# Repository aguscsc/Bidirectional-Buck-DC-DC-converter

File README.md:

# Bidirectional Buck DC-DC Converter

This repository documents the design and implementation of a **bidirectional DC-DC converter**.  
The system can operate in both **buck mode** (step-down) and **boost mode** (step-up), enabling power flow in both directions.  

---
## Software used
- **Simulation**
  
   Multisim, Ltspice and MATLAB/Simulink
   coil64
- **PCB**
  
   Kicad
## 📐 Specifications
- **Switching frequency**: 60 kHz  
- **Maximum power**: 5 W  

### Buck Mode
- $V_{in, min} = 23V$  
- $V_{out, max} = 14V$  

### Boost Mode
- $V_{in, min} = 12V$  
- $V_{out, max} = 27V$  

---

## 🔌 Topology
The selected topology is based on a **bidirectional synchronous buck/boost converter**.  
Diagram (preliminary):  

---

## 📊 Design Parameters
### Inductor
- To be dimensioned based on:  
 $L = \frac{V_L \cdot D}{\Delta I_L \cdot f_s}$
  where:
  - \( $V_L$ \) = inductor voltage  
  - \( $D$ \) = duty cycle  
  - \( $\Delta I_L$ \) = current ripple (≈ $30$% of \( $I_{L,max}$ \))  
  - \( $f_s$ \) = switching frequency
  
   $I_{sat} = \frac{B_{sat}\cdot l}{\mu_{0}\cdot \mu_{r}\cdot N}$
  Where:
  - \($I_{sat}$\) = Saturation current
  - \($B_{sat}$\) = saturation flux density of the core material
  - \($l$\) = effective magnetic path length of the core
  - \($\mu_{0}$\) = permeability of a vacuum
  - \($\mu_{r}$\) = relative permeability of the material
  - \($N$\) = number of turns

Recommendation: use coil64 to check your calculations, research skin effect and how different AWG interact with the frequency you're using (https://en.wikipedia.org/wiki/Skin_effect).
### Capacitor
- To be dimensioned from capacitor current balance:
- buck
  $C = \frac{\Delta I_L}{\Delta V \cdot f_s\cdot 8}$
- boost
  $C = \frac{I_{out} \cdot D}{\Delta V \cdot f_s}$
  
  where:
  - \( $\Delta V$ \) = allowed voltage ripple  

## Schematic & PCB layout

---
# Prototyping 
This section breaks down the process of prototyping and testing, the pcb in the design directory contains all the measures necessary to ensure the converter is working properly (value of components can be adjusted to your needs).
## BOM:
- 2 electrolytic capacitors $6.8\mu F$ and $2.2\mu F$ 50V each. 
- 2 ceramic capacitors (100nF).
- core T106-26 + 9m of AWG 26 wire (higher permeability would also work if the saturation stays sensible).
- 2 IFRZ44N (great for prototyping and testing)
- IR2184 driver (it can generate both MOSFET signals)
- 2 10 ohm gate resistors 1W (it limits the gate current)
- 2 10k ohm pull-down resistor 1W (drains the gate source capacitance)
 
## Measurements and tests
### switching
First, you ought to make sure the MOSFET are switching correctly. For this, turn on the pwm signal and your VCC source, then measure the gate-source pins of each MOSFET with an oscilloscope and make sure the signals are the complement of each other and respond to the change in duty. Aditionally, you should measure the gate current to ensure it is not exceeding the drivers capacity.

### Powering the circuit
Check the waveforms of the inductor current and output voltage, ideally you should be looking at two saw-like waves with minimal ripple.

Once you have ensured the inductor current and the output voltage have satisfied your needs you can proceed to measure the converters effiency for each mode.

Note: if you struggle achieving the voltage ripple required, considering soldering ceramic capacitors parallel to your current ones.
### Efficiency 
**BUCK** R = $39.8$

| Duty | $V_{in}$ | $I_{in}$ | $V_{out}$ | $P_{in}$ | $P_{out}$ | Efficiency |
|:----:|:---------:|:---------:|:----------:|:---------:|:----------:|:-----------:|
| 35%  | 23 V | 0.06 A | 7.26 V | 1.38 W | 1.32 W | 96.4 % |
| 45%  | 23 V | 0.10 A | 9.45 V | 2.30 W | 2.24 W | 97.5 % |
| 55%  | 23 V | 0.16 A | 11.6 V | 3.68 W | 3.38 W | 91.8 % |
| 65%  | 23 V | 0.22 A | 13.78 V | 5.06 W | 4.77 W | 94.3 % |

**BOOST** R = $142.2$

| Duty | $V_{in}$ | $I_{in}$ | $V_{out}$ | $P_{in}$ | $P_{out}$ | Efficiency |
|:----:|:---------:|:---------:|:----------:|:---------:|:----------:|:-----------:|
| 29.5%  | 12 V | 0.16 A | 16.34 V | 1.92 W | 1.87 W | 97.7 % |
| 39.5%  | 12 V | 0.21 A | 18.79 V | 2.52 W | 2.48 W | 98.5 % |
| 49.5%  | 12 V | 0.30 A | 22.11 V | 3.60 W | 3.43 W | 95.4 % |
| 59.5%  | 12 V | 0.46 A | 26.77 V | 5.52 W | 5.04 W | 91.3 % |

# PWM control
Previously, the pwm signal was generated with a waveform generator, for real applications this has to be implemented with a microcontroller, in this case we'll use a PIC32 to generate the pwm signal.
This section will cover the programming and testing of the control system and its integration with the power circuit.

## Prototyping

First the [Curiosity PIC32MZEF2](Datasheets/PIC32/Curiosity_PIC32MZEF2.0_Development_Board_Users_Guide_DS80005400A.pdf) board was used to program and debug the pic32, this board comes equipped with a PICKit on board 4 to program and the debug the microcontroller using [MPLABX](https://www.microchip.com/en-us/tools-resources/develop/mplab-x-ide).

To ensure the correct operation of the microcontroller, first it was configured to control the PWM signal via the analog to digital converter, mapping its input to duty cycle levels. The steps followed were:

```
+-----------------------+      +-----------------------+      +-----------------------+      +-----------------------+
|     Start: Create     |      |     Config Output     |----->|      Config Timer     |      |     End: Compile &    |
|  PWM Generation Code  |      |    Compare I/O Pins   |      |        Registers      |      |   Load Code to PIC32  |
+-----------------------+      +-----------------------+      +-----------------------+      +-----------------------+
            |                              ^                              |                              ^
            |                              |                              |                              |
            v                              |                              v                              |
+-----------------------+      +-----------------------+      +-----------------------+      +-----------------------+
|   Config Oscillator   |----->|     Config Output     |      |       Config the      |----->|     Init Remaining    |
|         & PLL         |      |     Compare Module    |      |           ADC         |      |    I/O & Peripherals  |
+-----------------------+      +-----------------------+      +-----------------------+      +-----------------------+
```
First, it is necessary to generate the system clock, to do this the POSC (primary Oscillator) was set to EC mode, generating a 12Mhz signal which was scaled using the PLL [data_sheets](/microcontroller/Datasheets), then feeding a voltage signal controlled with a potentiometer to the ADC the pwm signal was generated. 

Once peripherals were working as expected, a graphic interface was integrated to replace the potentiometer, allowing for control over the mode, duty and frequency at which the converter operated.

# Graphical Interface
To control the microcontroller used for the PWM signal, a graphical interface is designed, the criteria followed for the design were:

- Intuitive
- Easy to switch between modes
- Secure, it must limit human error as much as possible without harming the user's experience
- Use of non distracting colors
- It must have a visual representation of the signal and voltage output

To develop such interface the language chosen is Python, due to the presence of the library [Tkinter](https://docs.python.org/es/3/library/tkinter.html), which made the process a lot easier.

Here you can see the interface next to an example of a warning popup when going above the suggested operation point.

## How to use

### Executable
  
In [here](/microcontroller/graphic_interface/executables) you will find executables to run on your machine (Linux and Windows are currently supported).

### Manual

**1. Clone the repository**

```
git clone https://github.com/aguscsc/Bidirectional-Buck-DC-DC-converter.git
cd Bidirectional-Buck-DC-DC-converter/microcontroller/graphic_interface
```

**2. Dependencies**

```
pip install pyserial
```

**3. Run gui.py**

```
python gui.py
```

**Spanish version**

```
python es_gui.py
```

## Final PCB

The final PCB design consolidates all previously discussed subsystems into a single, compact board. It integrates the custom power stage, two voltage regulators to supply the gate driver and the PIC32 microcontroller, and a USB-C port to interface with the graphical control software.

## ESP32 Telemetry & Sensing
To enable real-time monitoring, an **ESP32** module acts as a wireless telemetry unit. It senses input/output voltages and transmits data back to the Graphical Interface via Wi-Fi, allowing for remote performance tracking without physical probes.

### ⚡ Signal Conditioning (Voltage Divider)
The ESP32 GPIOs are not 5V tolerant and operate at a **3.3V logic level**. Since the converter handles up to 27V, voltage dividers are mandatory to scale the signals into the ADC's linear range ($100\text{mV}$ to $2.45\text{V}$ at $12\text{dB}$ attenuation).

The scaling follows the voltage divider formula:

$$V_{adc} = V_{out} \cdot \left( \frac{R_2}{R_1 + R_2} \right)$$

**Recommended Resistor Values:**
| Target Rail | Max Voltage | $R_1$ (Source) | $R_2$ (GND) | Divider Ratio | Max $V_{adc}$ |
| :--- | :--- | :--- | :--- | :--- | :--- |
| **Buck Output** | 14V | $47\text{k}\Omega$ | $10\text{k}\Omega$ | $0.175$ | $2.45\text{V}$ |
| **Boost Output** | 27V | $100\text{k}\Omega$ | $10\text{k}\Omega$ | $0.091$ | $2.45\text{V}$ |

> [!WARNING]
> Always verify the divider output with a multimeter before connecting to the ESP32. Overvoltage will permanently damage the SoC.

### 🌐 Wireless Protocol: UDP
We implemented the **UDP (User Datagram Protocol)** for data transmission:
* **Low Latency:** Unlike TCP, UDP does not require a handshake, making it ideal for high-frequency telemetry updates.
* **Efficiency:** Smaller packet overhead reduces the power consumption and processing time of the ESP32.

### 🛠️ Software Configuration (ESP-IDF)
The firmware is built using the **ESP-IDF v5.x** framework. To integrate it with your local network, modify the constants in `main/main.c`:

```c
// --- USER CONFIGURATION ---
#define WIFI_SSID      "Your_SSID"
#define WIFI_PASS      "Your_Password"
#define PC_IP_ADDR     "192.168.1.XX" // Your PC's local IP
#define PORT           3333           // Must match GUI port
---

**Deployment:**

1. Connect the ESP32 via USB.
2. Initialize the environment: `. $HOME/esp/esp-idf/export.sh`
3. Build and flash:
```bash
idf.py build flash monitor

```
### ESP32 PCB

Additionally a pcb was desgined to use the telemetry ssitem as an add-on to the converter

---
## 👥 Collaborators
- **[Agustín Torres](https://github.com/aguscsc)**  
- **[Ignacio Cerda](https://github.com/LovesCharlie)**  
- **[Gian Luca Barbagelata](https://github.com/Yian-n)**  

---

## 📚 References
-   Mohan – Power Electronics, Cap. 7
-   Erickson – Fundamentals of Power Electronics, Cap. 3
-   Power Electronics: Converters, Applications, and Design” – Ned Mohan
-   Electronica de Potencia, 1era edicion - Daniel W.Hart

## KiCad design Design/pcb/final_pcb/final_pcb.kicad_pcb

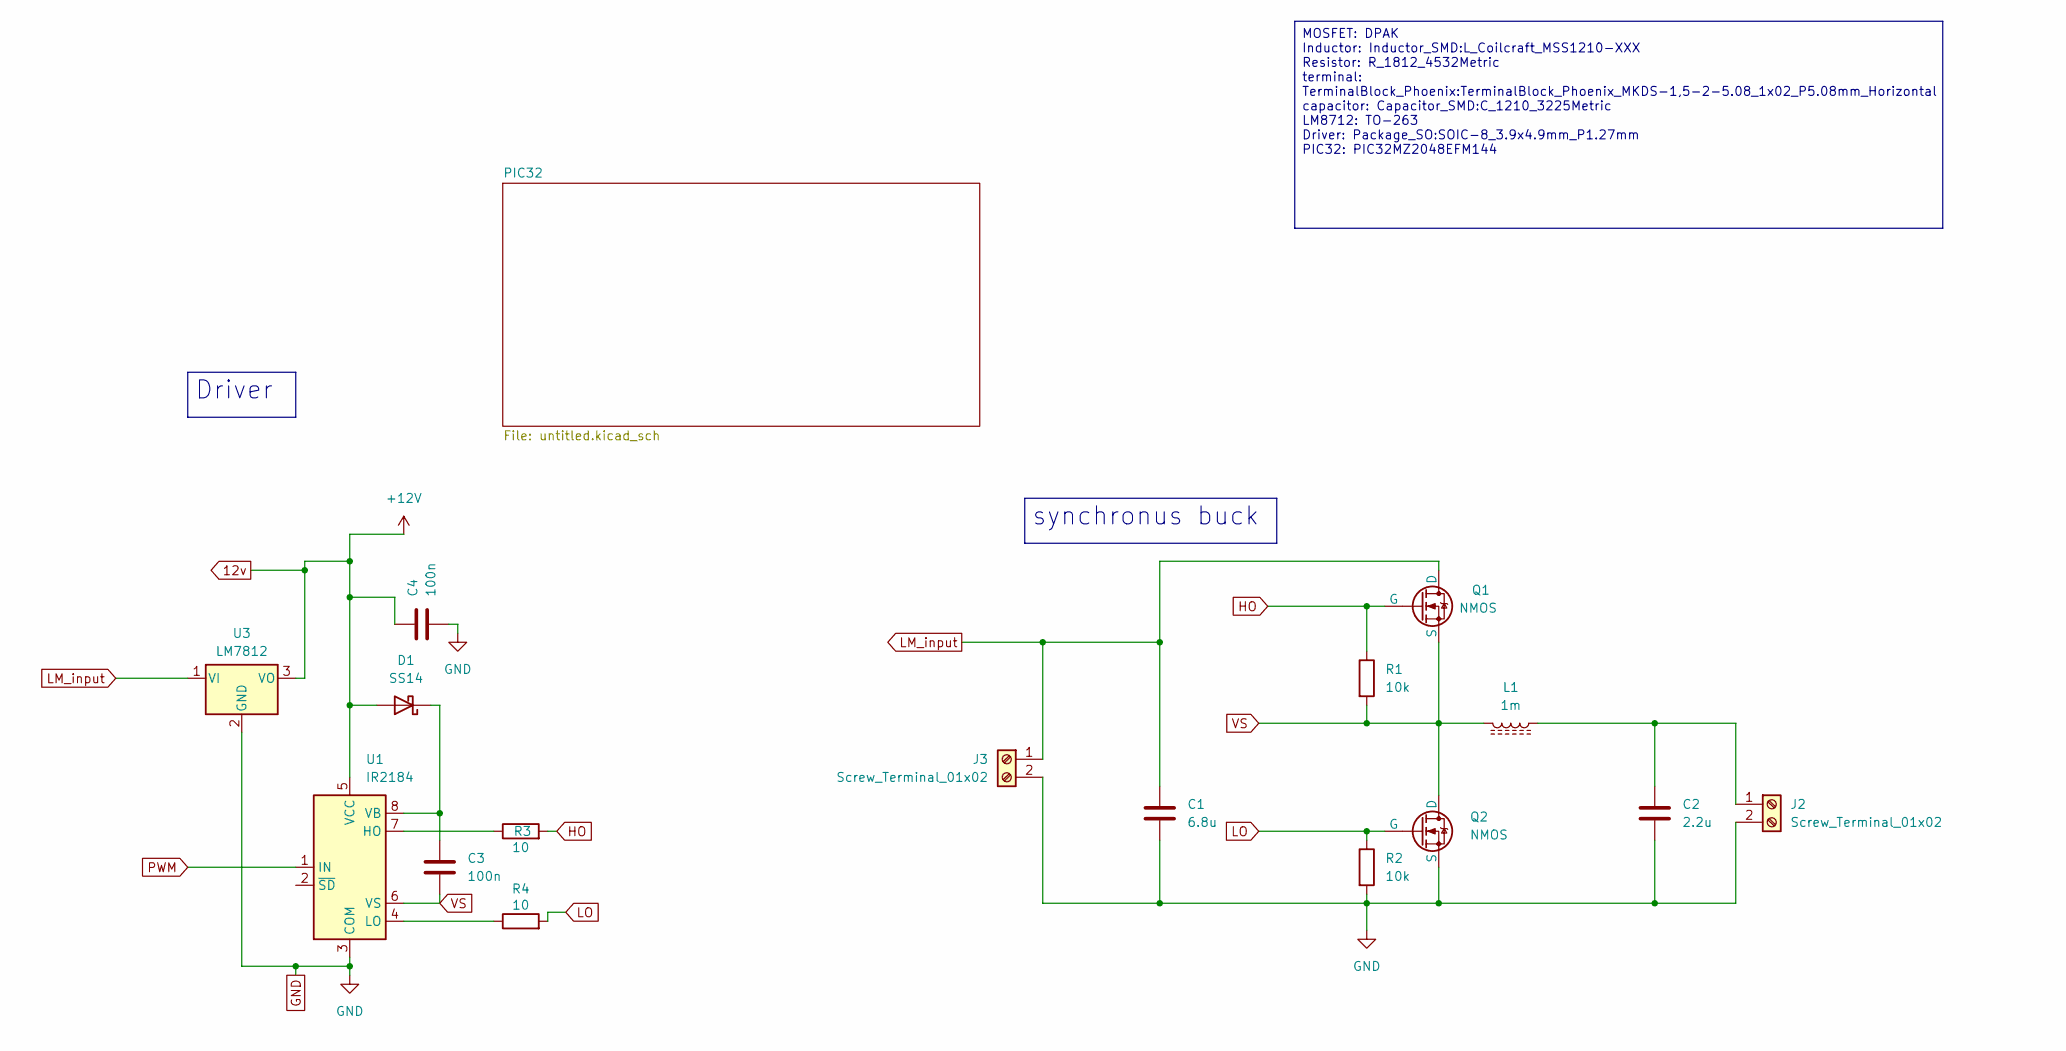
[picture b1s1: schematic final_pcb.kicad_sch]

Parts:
C1: 6.8u; C_1210_3225Metric
C2: 2.2u; C_1210_3225Metric
C3, C4: 100n; C_1210_3225Metric
D1: SS14; D_SMA
J2, J3: Screw_Terminal_01x02; TerminalBlock_Phoenix_PTSM-0,5-2-2,5-V-SMD_1x02-1MP_P2.50mm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
L1: 1m; L_Coilcraft_MSS1210-XXX
Q1, Q2: NMOS; TO-252-2
R1, R2: 10k; R_1812_4532Metric
R3, R4: 10; R_1812_4532Metric
U1: IR2184; SOIC-8_3.9x4.9mm_P1.27mm
U3: LM7812; TO-263-3_TabPin2

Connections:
12v: C4.1, D1.2 (A), U1.5 (VCC), U3.3 (VO); also elsewhere on the board
GND: C1.2, C2.2, C4.2, J2.2, J3.2, Q2.3 (S), R2.2, U1.3 (COM), U3.2 (GND); also elsewhere on the board
HO: Q1.2 (G), R1.1, R3.2
LM_input: C1.1, J3.1, Q1.1 (D), U3.1 (VI)
LO: Q2.2 (G), R2.1, R4.2
unnamed: C3.1, D1.1 (K), U1.8 (VB)
unnamed: C2.1, J2.1, L1.1
unnamed: R3.1, U1.7 (HO)
unnamed: R4.1, U1.4 (LO)
PWM: U1.1 (IN); also elsewhere on the board
VS: C3.2, L1.2, Q1.3 (S), Q2.1 (D), R1.2, U1.6 (VS)

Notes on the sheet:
MOSFET: DPAK Inductor: Inductor_SMD:L_Coilcraft_MSS1210-XXX Resistor: R_1812_4532Metric terminal: TerminalBlock_Phoenix:TerminalBlock_Phoenix_MKDS-1,5-2-5.08_1x02_P5.08mm_Horizontal capacitor: Capacitor_SMD:C_1210_3225Metric LM8712: TO-263 Driver: Package_SO:SOIC-8_3.9x4.9mm_P1.27mm PIC32: PIC32MZ2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
Driver
synchronus buck

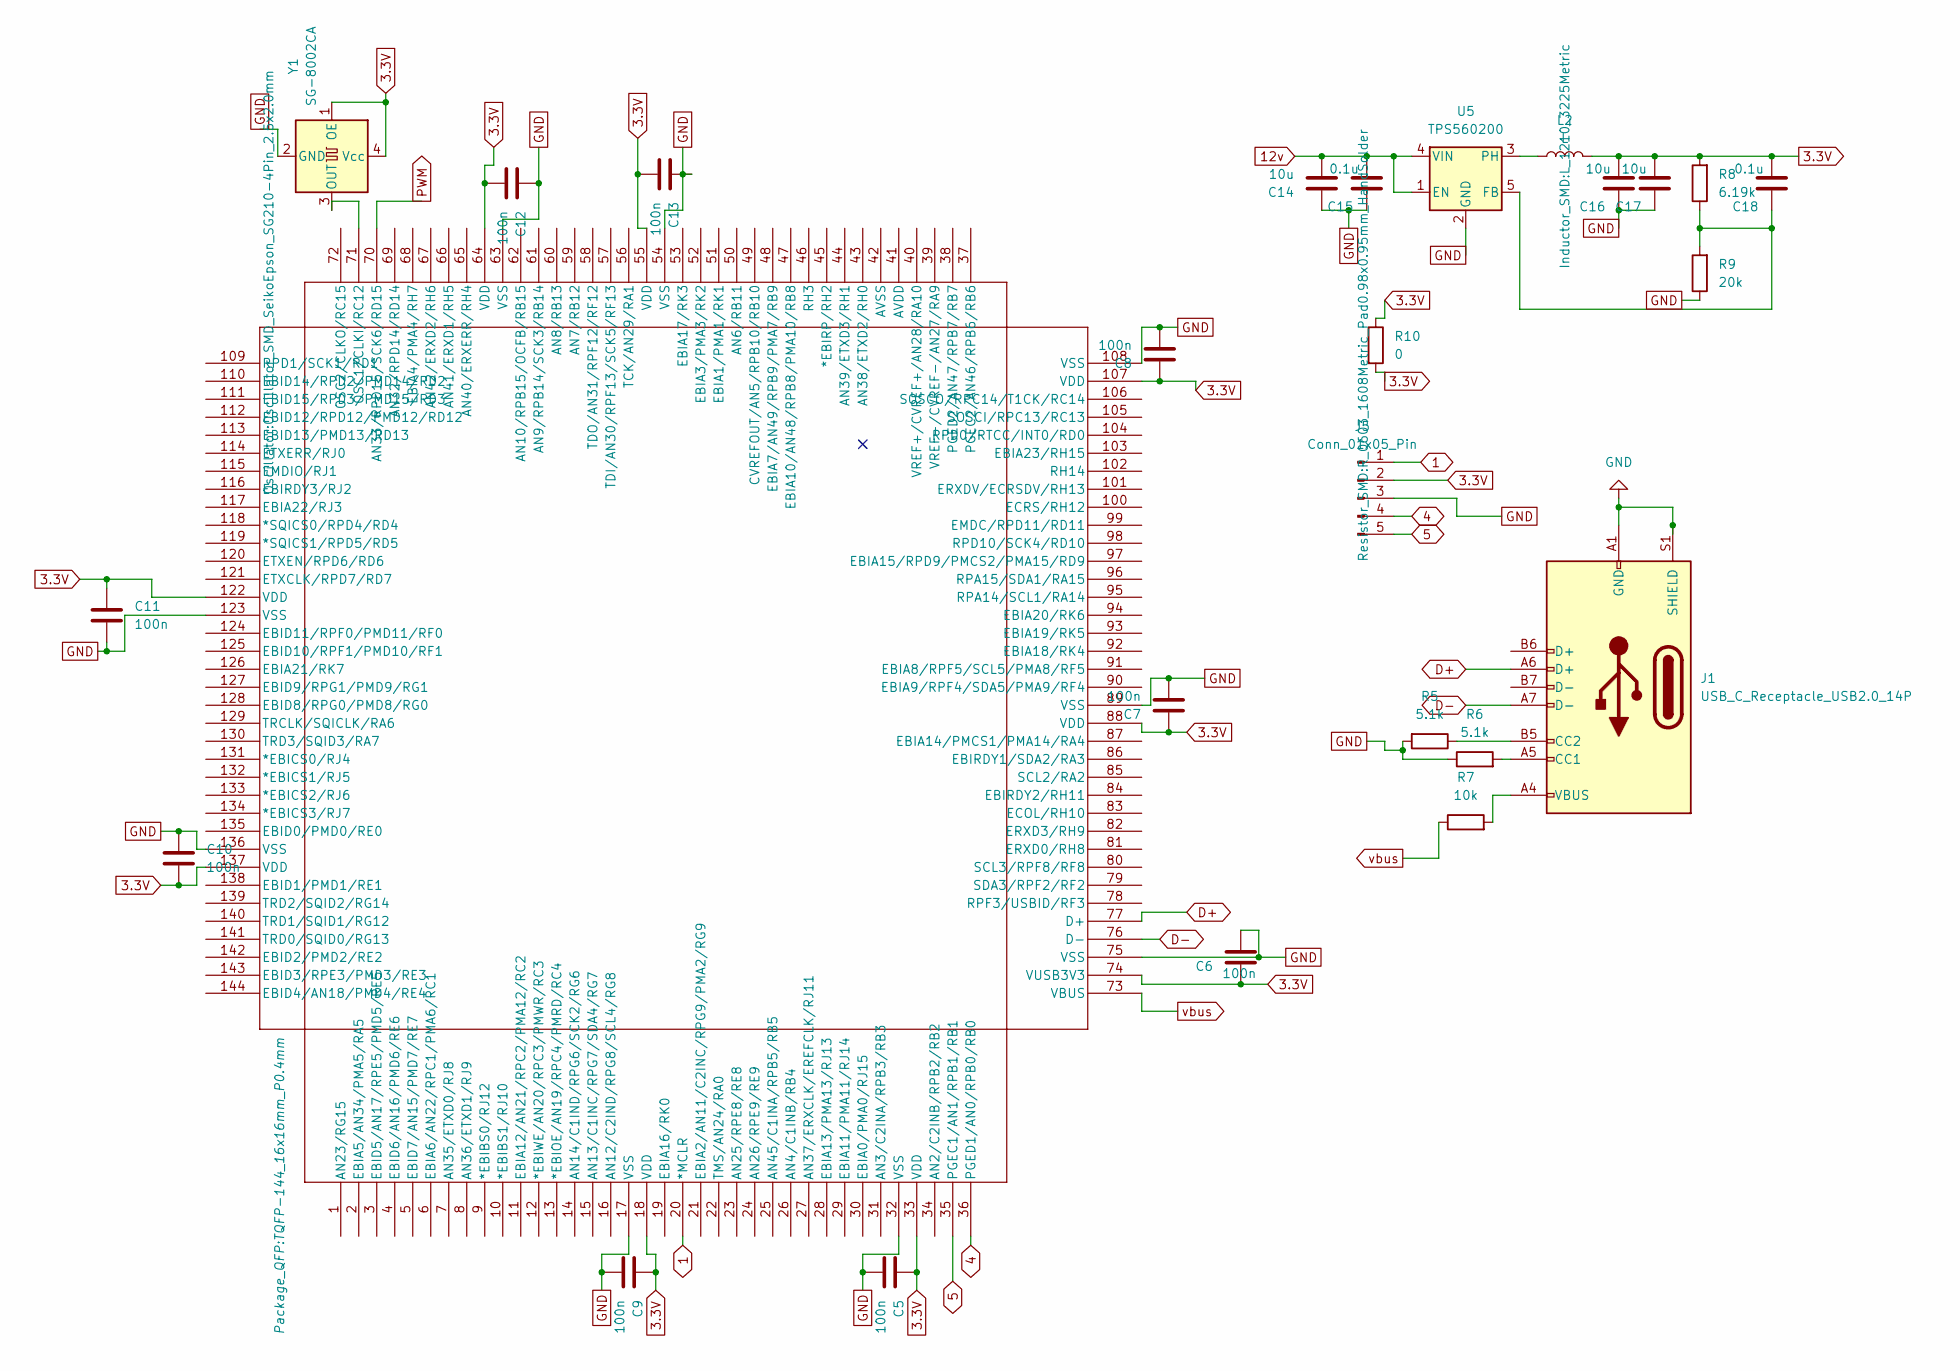
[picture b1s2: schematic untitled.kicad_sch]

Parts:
C5, C6, C7, C8, C9, C10, C11, C12, C13: 100n; C_1210_3225Metric
C14, C16, C17: 10u; C_1210_3225Metric
C15, C18: 0.1u; C_1210_3225Metric
J1: USB_C_Receptacle_USB2.0_14P; USB_C_Receptacle_GCT_USB4110
J5: Conn_01x05_Pin; PinHeader_1x05_P2.54mm_Vertical_SMD_Pin1Left
L2: L; L_1210_3225Metric
R5, R6: 5.1k; R_1812_4532Metric
R7: 10k; R_1812_4532Metric
R8: 6.19k; R_1812_4532Metric
R9: 20k; R_1812_4532Metric
R10: 0; R_0603_1608Metric_Pad0.98x0.95mm_HandSolder
U2: PIC32MZ2048EFM144-I/PH; TQFP-144_16x16mm_P0.4mm
U5: TPS560200; SOT-23-5
Y1: SG-8002CA; Oscillator_SMD_SeikoEpson_SG210-4Pin_2.5x2.0mm

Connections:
1: J5.1, U2.20 (*MCLR)
3.3V: C5.1, C6.1, C7.1, C8.1, C9.1, C10.2, C11.1, C12.2, C13.2, C16.2, C17.2, C18.2, J5.2, L2.2, R8.2, R10.1, R10.2, U2.18 (VDD), U2.33 (VDD), U2.55 (VDD), U2.64 (VDD), U2.74 (VUSB3V3), U2.88 (VDD), U2.107 (VDD), U2.122 (VDD), U2.137 (VDD), Y1.1 (OE), Y1.4 (Vcc)
4: J5.4, U2.36 (PGED1/AN0/RPB0/RB0)
5: J5.5, U2.35 (PGEC1/AN1/RPB1/RB1)
12v: C14.2, C15.2, U5.1 (EN), U5.4 (VIN); also elsewhere on the board
D+: J1.A6 (D+), U2.77 (D+)
D-: J1.A7 (D-), U2.76 (D-)
GND: C5.2, C6.2, C7.2, C8.2, C9.2, C10.1, C11.2, C12.1, C13.1, C14.1, C15.1, C16.1, C17.1, J1.A1 (GND), J1.A12 (GND), J1.B1 (GND), J1.B12 (GND), J1.S1 (SHIELD), J5.3, R5.2, R6.1, R9.1, U2.17 (VSS), U2.32 (VSS), U2.54 (VSS), U2.63 (VSS), U2.75 (VSS), U2.89 (VSS), U2.108 (VSS), U2.123 (VSS), U2.136 (VSS), U5.2 (GND), Y1.2 (GND); also elsewhere on the board
unnamed: J1.A5 (CC1), R6.2
unnamed: J1.B5 (CC2), R5.1
unnamed: J1.A4 (VBUS), J1.A9 (VBUS), J1.B4 (VBUS), J1.B9 (VBUS), R7.2
unnamed: U2.71 (OSC1/CLKI/RC12), Y1.3 (OUT)
unnamed: C18.1, R8.1, R9.2, U5.5 (FB)
unnamed: L2.1, U5.3 (PH)
PWM: U2.70 (AN33/RPD15/SCK6/RD15); also elsewhere on the board
vbus: R7.1, U2.73 (VBUS)

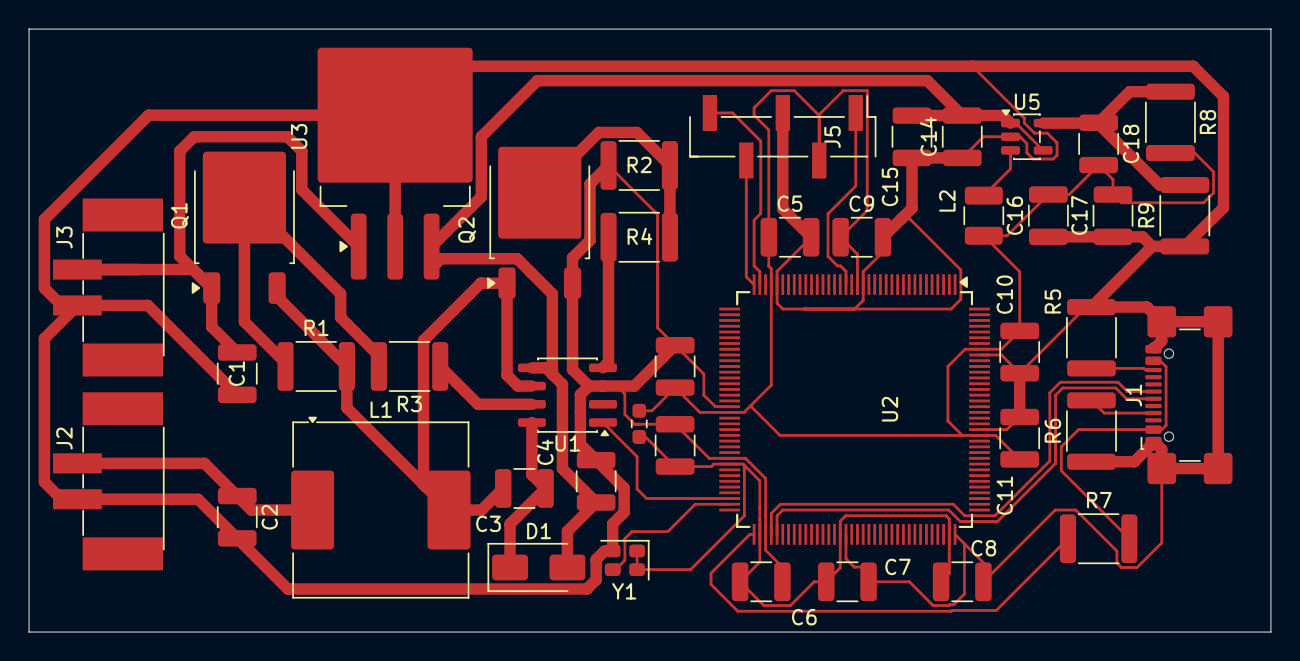
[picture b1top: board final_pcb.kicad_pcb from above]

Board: 2 copper layers, 86.5 x 42.0 mm, 42 parts (0 on the bottom side), 24 nets.

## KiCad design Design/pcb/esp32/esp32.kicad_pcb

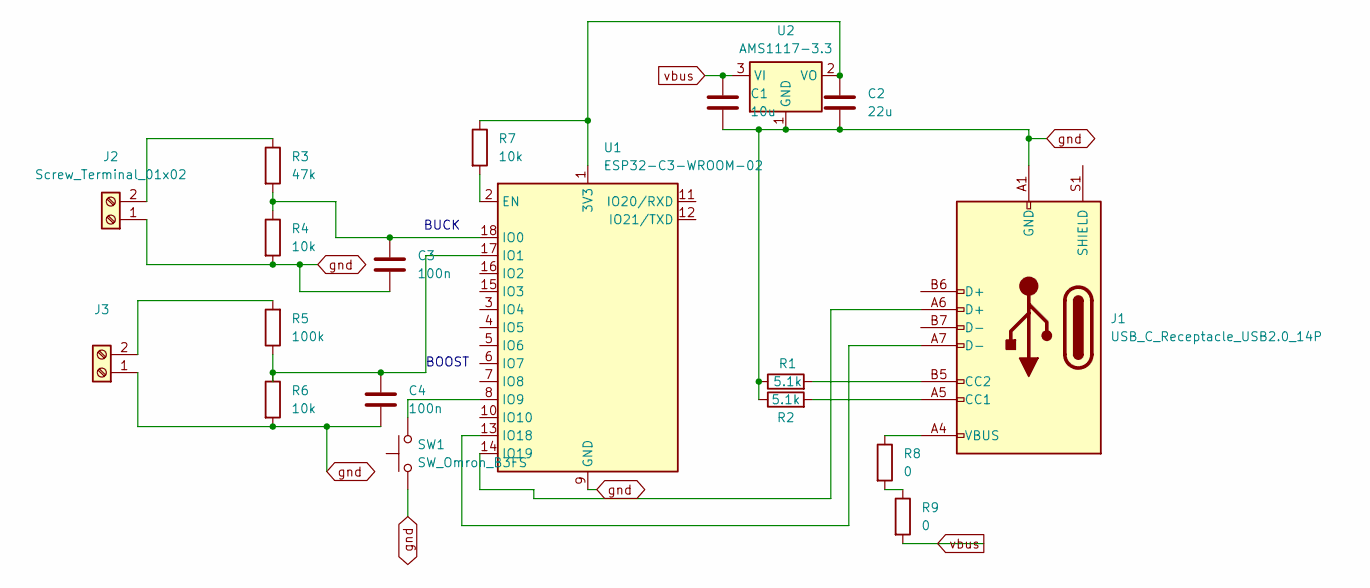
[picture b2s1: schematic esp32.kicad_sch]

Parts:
C1: 10u; C_0603_1608Metric
C2: 22u; C_0603_1608Metric
C3, C4: 100n; C_0603_1608Metric
J1: USB_C_Receptacle_USB2.0_14P; USB_C_Receptacle_GCT_USB4105-xx-A_16P_TopMnt_Horizontal
J2, J3: Screw_Terminal_01x02; TerminalBlock_Phoenix_MKDS-1,5-2-5.08_1x02_P5.08mm_Horizont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
R1, R2: 5.1k; R_0402_1005Metric
R3: 47k; R_0402_1005Metric
R4: 10k; R_0402_1005Metric_Pad0.72x0.64mm_HandSolder
R5: 100k; R_0402_1005Metric
R6, R7: 10k; R_0402_1005Metric
R8, R9: 0; R_1206_3216Metric
SW1: SW_Omron_B3FS; SW_SPST_Omron_B3FS-100xP
U1: ESP32-C3-WROOM-02
U2: AMS1117-3.3; SOT-223-3_TabPin2

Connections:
unnamed: J1.A5 (CC1), R2.2
unnamed: J1.B5 (CC2), R1.2
unnamed: J1.A4 (VBUS), J1.A9 (VBUS), J1.B4 (VBUS), J1.B9 (VBUS), R8.1
unnamed: J2.2, R3.1
unnamed: J3.2, R5.2
unnamed: R8.2, R9.1
unnamed: C2.1, R7.1, U1.1 (3V3), U2.2 (VO)
unnamed: R7.2, U1.2 (EN)
unnamed: C3.1, R3.2, R4.1, U1.18 (IO0)
unnamed: C4.1, R5.1, R6.1, U1.17 (IO1)
unnamed: SW1.2, U1.8 (IO9)
unnamed: J1.A7 (D-), U1.13 (IO18)
unnamed: J1.A6 (D+), U1.14 (IO19)
gnd: C1.2, C2.2, C3.2, C4.2, J1.A1 (GND), J1.A12 (GND), J1.B1 (GND), J1.B12 (GND), J2.1, J3.1, R1.1, R2.1, R4.2, R6.2, SW1.1, U1.9 (GND), U1.19 (GND), U2.1 (GND)
vbus: C1.1, R9.2, U2.3 (VI)

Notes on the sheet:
BOOST
BUCK

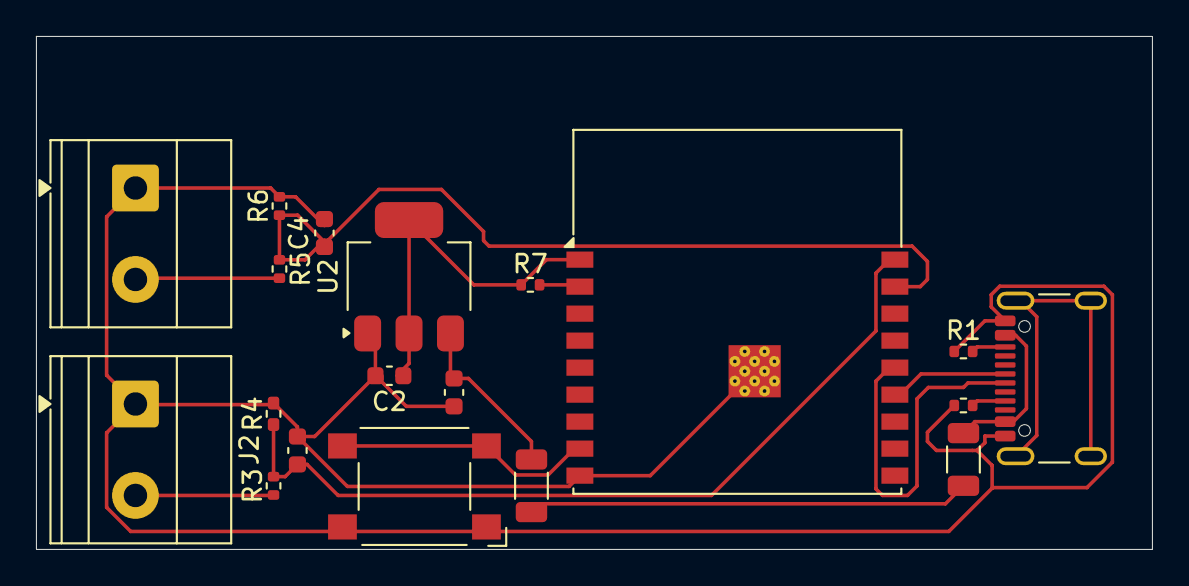
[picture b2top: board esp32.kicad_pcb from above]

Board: 2 copper layers, 62.0 x 28.5 mm, 19 parts (0 on the bottom side), 15 nets.

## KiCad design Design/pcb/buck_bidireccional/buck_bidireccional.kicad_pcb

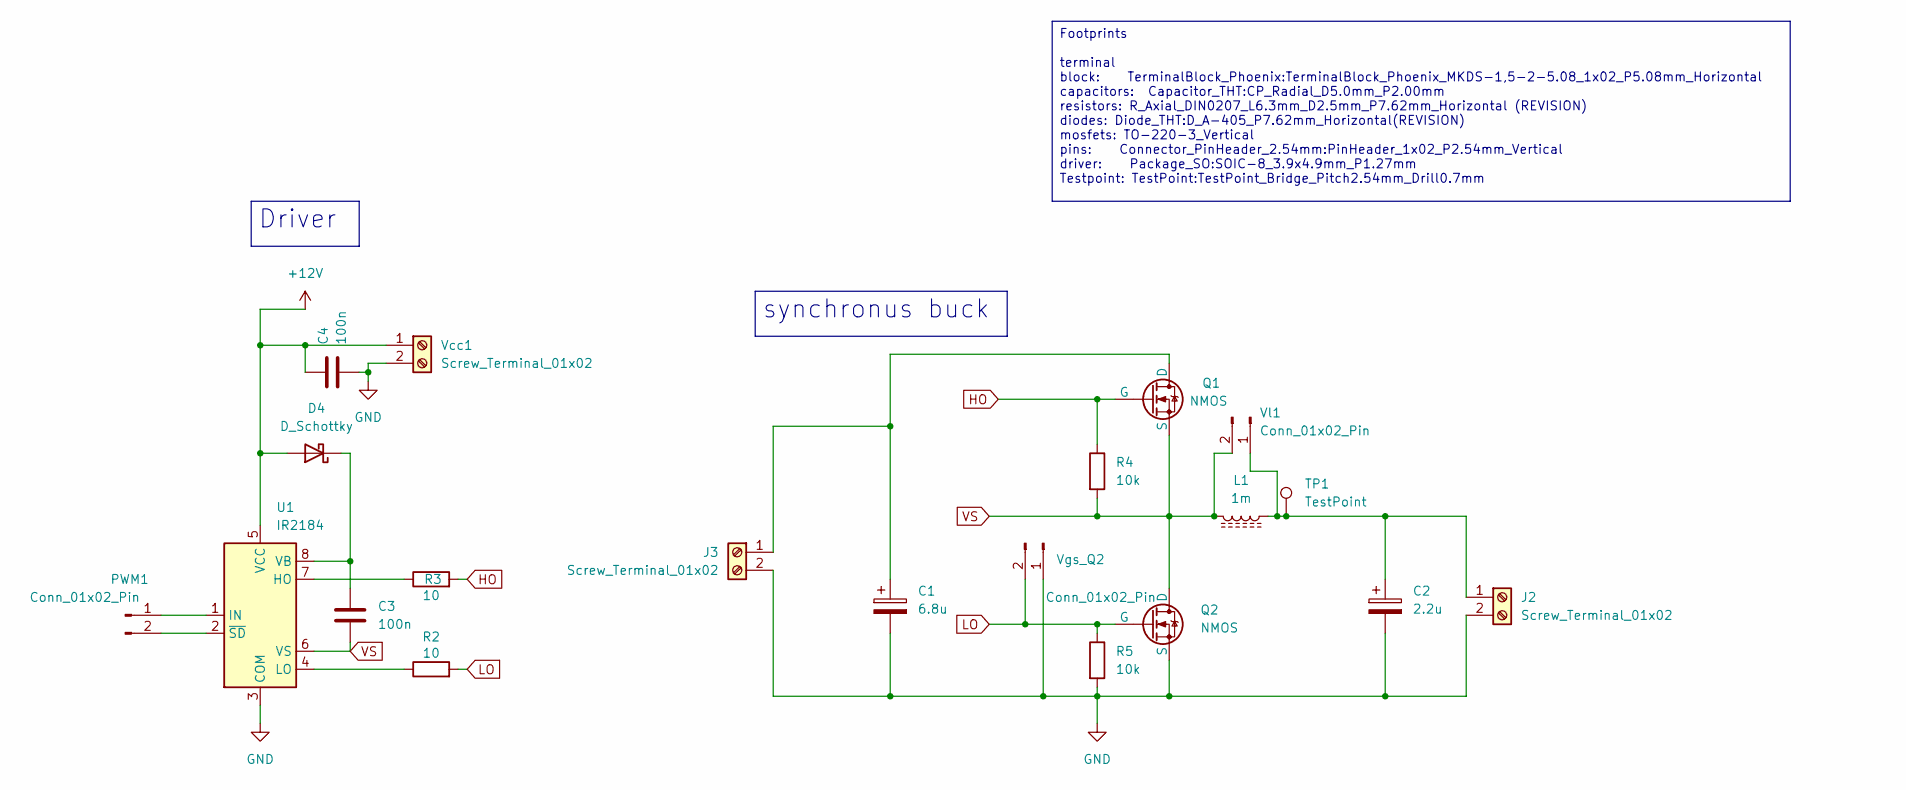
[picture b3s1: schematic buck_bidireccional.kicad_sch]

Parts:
C1: 6.8u; CP_Radial_D5.0mm_P2.00mm
C2: 2.2u; CP_Radial_D5.0mm_P2.00mm
C3, C4: 100n; CP_Radial_D5.0mm_P2.00mm
D4: D_Schottky; D_A-405_P7.62mm_Horizontal
J2, J3: Screw_Terminal_01x02; TerminalBlock_Phoenix_MKDS-1,5-2-5.08_1x02_P5.08mm_Horizont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
L1: 1m; buck_inductor
PWM1: Conn_01x02_Pin; PinHeader_1x02_P2.54mm_Vertical
Q1, Q2: NMOS; TO-220-3_Vertical
R2, R3: 10; R_Axial_DIN0207_L6.3mm_D2.5mm_P7.62mm_Horizontal
R4, R5: 10k; R_Axial_DIN0207_L6.3mm_D2.5mm_P7.62mm_Horizontal
TP1: TestPoint; TestPoint_Bridge_Pitch5.08mm_Drill1.3mm
U1: IR2184; SOIC-8_3.9x4.9mm_P1.27mm
Vcc1: Screw_Terminal_01x02; TerminalBlock_Phoenix_MKDS-1,5-2-5.08_1x02_P5.08mm_Horizont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
Vgs_Q2: Conn_01x02_Pin; PinHeader_1x02_P2.54mm_Vertical
Vl1: Conn_01x02_Pin; PinHeader_1x02_P2.54mm_Vertical

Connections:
+12V: C4.1, D4.2 (A), U1.5 (VCC), Vcc1.1
GND: C1.2, C2.2, C4.2, J2.2, J3.2, Q2.3 (S), R5.2, U1.3 (COM), Vcc1.2, Vgs_Q2.1
HO: Q1.2 (G), R3.2, R4.1
LO: Q2.2 (G), R2.2, R5.1, Vgs_Q2.2
unnamed: C3.1, D4.1 (K), U1.8 (VB)
unnamed: C2.1, J2.1, L1.1, TP1.1, Vl1.1
unnamed: C1.1, J3.1, Q1.1 (D)
unnamed: PWM1.1, U1.1 (IN)
unnamed: PWM1.2, U1.2 (~SD)
unnamed: R3.1, U1.7 (HO)
unnamed: R2.1, U1.4 (LO)
VS: C3.2, L1.2, Q1.3 (S), Q2.1 (D), R4.2, U1.6 (VS), Vl1.2

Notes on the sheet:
synchronus buck
Driver
Footprints terminal block: TerminalBlock_Phoenix:TerminalBlock_Phoenix_MKDS-1,5-2-5.08_1x02_P5.08mm_Horizontal capacitors: Capacitor_THT:CP_Radial_D5.0mm_P2.00mm resistors: R_Axial_DIN0207_L6.3mm_D2.5mm_P7.62mm_Horizontal (REVISION) diodes: Diode_THT:D_A-405_P7.62mm_Horizontal(REVISION) mosfets: TO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

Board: 2 copper layers, 20 parts (1 on the bottom side), 12 nets, no tracks yet.

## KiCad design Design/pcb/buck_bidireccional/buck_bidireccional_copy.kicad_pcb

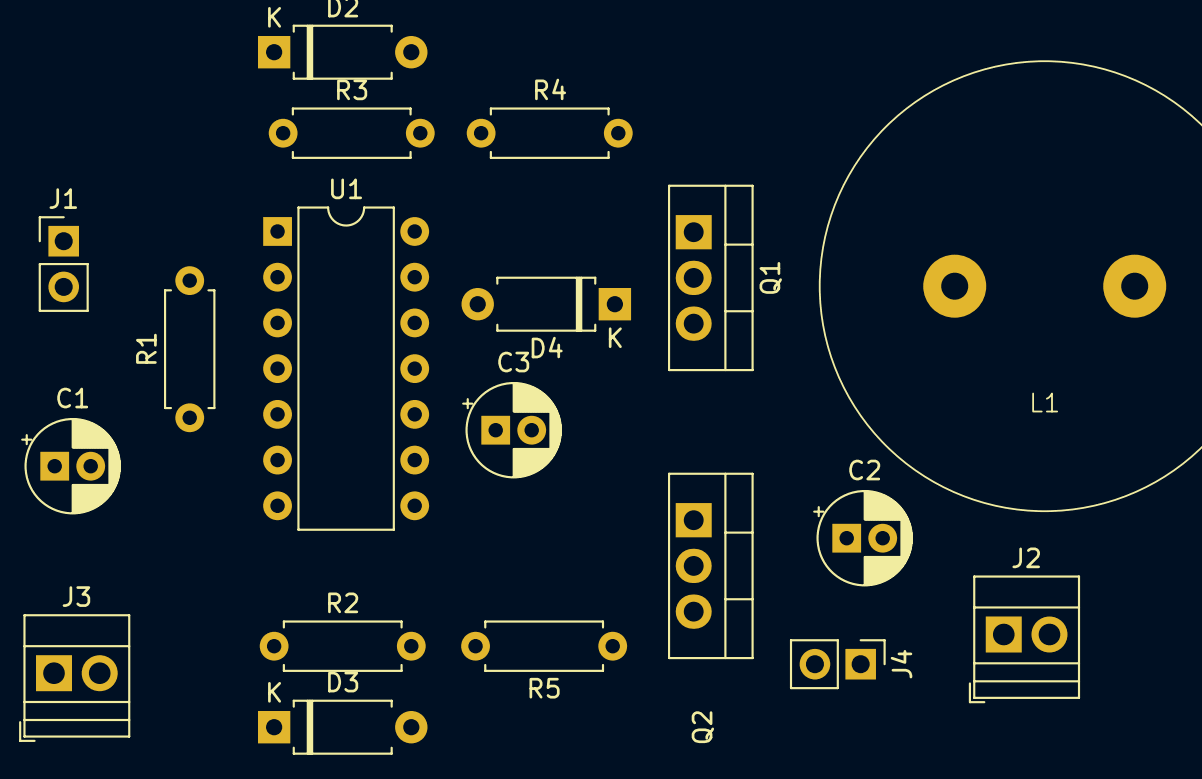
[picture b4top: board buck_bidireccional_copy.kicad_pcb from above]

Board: 2 copper layers, 19 parts (0 on the bottom side), 12 nets, no tracks yet.

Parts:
C1: 6.8u; CP_Radial_D5.0mm_P2.00mm
C2: 2.2u; CP_Radial_D5.0mm_P2.00mm
C3: 100n; CP_Radial_D5.0mm_P2.00mm
D2, D3, D4: D_Schottky; D_A-405_P7.62mm_Horizontal
J1, J4: Conn_01x02_Pin; PinHeader_1x02_P2.54mm_Vertical
J2, J3: Screw_Terminal_01x02; TerminalBlock_Xinya_XY308-2.54-2P_1x02_P2.54mm_Horizontal
L1: 1m; buck_inductor
Q1, Q2: NMOS; TO-220-3_Vertical
R1: 10k; R_Axial_DIN0207_L6.3mm_D2.5mm_P7.62mm_Horizontal
R2, R3: 10; R_Axial_DIN0207_L6.3mm_D2.5mm_P7.62mm_Horizontal
R4, R5: 100k; R_Axial_DIN0207_L6.3mm_D2.5mm_P7.62mm_Horizontal
U1: IR2184; DIP-14_W7.62mm

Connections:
+12V: D4.2 (A), R1.1, U1.5 (VCC)
GND: C1.2, C2.2, J2.2, J3.2, Q2.3 (S), R5.2, U1.3 (COM)
unnamed: D2.2 (A), Q1.2 (G), R3.2, R4.1
unnamed: D2.1 (K), R3.1, U1.7 (HO)
unnamed: D3.2 (A), Q2.2 (G), R2.2, R5.1
unnamed: D3.1 (K), R2.1, U1.4 (LO)
unnamed: C3.1, D4.1 (K), U1.8 (VB)
unnamed: J1.1, U1.1 (IN)
unnamed: J1.2, R1.2, U1.2 (~SD)
unnamed: C2.1, J2.1, J4.1, L1.1
unnamed: C1.1, J3.1, Q1.1 (D)
unnamed: C3.2, J4.2, L1.2, Q1.3 (S), Q2.1 (D), R4.2, U1.6 (VS)

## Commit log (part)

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2025-08-28 Create Design
2025-08-28 Create mul
2025-08-28 MATLAB_CALC
2025-08-28 Add files via upload
    SWITCHES simulation
2025-08-28 Create kicadhere
2025-08-28 Create matcadhere
2025-08-29 Create desc
2025-08-29 file extension
2025-08-30 Move files
2025-08-31 NACHO
    simulink circuito
2025-08-31 Nacho
    Mathcad del buck bidireccional
2025-08-31 sim en proteus con driver
2025-08-31 Nacho
    Agreado osciloscopio para medicion de voltaje de gates
2025-08-31 Nacho
    Agregada referencia de libro EPO
2025-08-31 Nacho
    Verificando valores
2025-09-01 Update README.md
    optoacople
2025-09-01 nacho
    SIMULINK CON VALORES DE CALCULO
2025-09-01 nACHO
    agregada la referencia del libro
2025-09-01 Nacho
    Analisis de casos, se obtuvo:
    para modo buck Vomax=12.9[V]
    para modo Boost Vomax=30[V]
2025-09-02 sim proteus
2025-09-02 Nacho
    Meh
2025-09-02 Nacho
    Cambios de valores
2025-09-02 Nacho
    Documento con componentes
2025-09-02 added datasheet
2025-09-02 datasheet update
    added possible driver datasheet
2025-09-02 octocoupler
    no octocoupler
2025-09-03 adjust 1% voltage ripple
2025-09-04 update mathcad, Rpd calcs
    100kohm pulldown resistor calc
2025-09-04 kicad first try
    pcb aint pcbing yet
2025-09-04 Updated kicad
    still needs fixes
2025-09-05 updated pcb
2025-09-05 updates kiskas
2025-09-06 Parte teorica del MOSFET
    Lo más basico, voy complementando a medida que avance
2025-09-07 Teoria del mosfet
    FUNCIONAMIENTO DETALLADO DEL MOSFET
2025-09-08 Cambios a MOSFET real
    Se ajusto al mosfet IRFZ44N y agregado valores de capacitores a utilizar
2025-09-08 Cambio a un duty de 60% en Boost
2025-09-08 cambio sim
2025-09-08 nada
2025-09-09 update kicad
2025-09-09 Coloqué mediciones de componentes en proteus
2025-09-09 Agregué calculos del numero de vueltas de la bobina
2025-09-09 updated kicad
    MOSFET gate oscilloscope reading still missing
2025-09-09 Agregado un voltemeter
2025-09-11 final update pcb
2025-09-11 kicad pdf
2025-09-11 final kicad
2025-09-11 g1 to g2
2025-09-12 Meh
    No me acuerdo que eran
2025-09-12 final pcb
2025-09-15 update kicad + gerber
2025-09-15 mathcad correction
2025-09-21 update Rg calc
2025-09-22 cap V update
2025-09-22 added preliminary efficiency simulation
2025-09-23 Carta Gantt
2025-09-24 Datasheet del pic32
2025-09-24 Orden de la simulacion y agregado de capacitancias parasitas
2025-09-24 Eleccion de VDSMAX en MOSFETS
2025-09-25 Pérdidas y eficiencia
2025-09-25 fixed pic
2025-09-25 removed non needed resistors
2025-09-25 fixed ids
2025-09-25 added stuff
2025-09-25 added boost mode
2025-09-25 Datasheet del diodo
2025-09-26 a lot of stuff
2025-09-27 schem update
2025-09-27 update for pcbway
2025-09-30 Agregado TODOs
2025-10-01 fixed kicad error
2025-10-05 erased extra dash
2025-10-05 added pic32 folder
2025-10-05 mish
2025-10-05 secs
2025-10-06 fixed efficiency code
2025-10-06 saque pulldown y diodo
2025-10-10 edited gate resistors out due to them being fed by external vcc, ESR values must be re-checked
2025-10-12 fixed pcb
2025-10-12 updated pics
2025-10-16 coil64
2025-10-18 Enhance README with prototyping section and BOM
    Added a new section on prototyping and updated BOM details in the README.
2025-10-18 merge
2025-10-18 some
2025-10-18 Fix formatting and enhance README content
    Corrected formatting issues and improved clarity in the README. Added images and sections for measurements and tests.
2025-10-18 Update README with circuit powering instructions
    Added a section on powering the circuit and measuring efficiency.
2025-10-18 Add MIT License to the project
2025-10-19 slight fix
2025-10-20 added test notes
2025-10-21 added pics and table (early push due to pics being needed)
2025-10-21 fixed tables
2025-10-21 Add BOOST R and efficiency table to README
2025-10-21 Fix power values in efficiency table
    Updated input and output power values for 45% and 65% duty cycles in the efficiency table.
2025-10-21 Add note on ceramic capacitors for voltage ripple
    Added note about using ceramic capacitors for voltage ripple issues.
2025-10-21 Improve README with updated images and PWM control section
    Updated image alt text for clarity and added a new section on PWM control.
2025-10-22 updates to kicad
2025-10-22 updaete
2025-10-24 Ppt de la presentacion y excel con datos teoricos y practicos
2025-10-27 compresed images and added graphical interface code
2025-10-27 fixed readme
2025-11-05 new gui
2025-11-07 added warnings to the gui
2025-11-07 added baud rate
2025-11-07 fixed log
2025-11-07 First teste graphical interface using arduino nano
2025-11-07 gui pics
2025-11-07 fixed typo
2025-11-07 addded spanish version for the interface
2025-11-07 Fix comment formatting for dutyCycle variable
2025-11-08 cleaned up gui (still in revision)
2025-11-08 Update README with dependencies and usage instructions
    Added dependencies and usage instructions for the project.
2025-11-08 Increase image widths in README.md
    Updated image widths in README for better visibility.
2025-11-11 Datasheets del PIC32
2025-11-11 proyecto PIC32 de cuando se hizo en microelectronica
2025-11-11 codigo y datasheets
2025-11-20 touch up to gui
2025-11-20 fixed bugs
2025-11-20 code para la el pic con la gui
2025-11-21 gui gui
2025-11-21 merger
2025-11-21 matcad.pdf
2025-11-22 gui update
2025-11-22 executable linux
2025-11-22 windows executable
2025-11-22 Update README with usage and executable information
    Added usage instructions and executable details to README.
2025-11-23 fixed frozen buttons
2025-11-23 changes to executables
2025-11-23 Mac executable
2025-11-23 cleand up readme and gui
2025-11-23 Revise PWM generation flowchart and system clock details
    Updated the flowchart for PWM generation steps and clarified the system clock generation process.
2025-11-23 nam efix
2025-11-23 empty
2025-12-03 start final pcb
2025-12-03 Cambio a slider de frecuencia
2025-12-03 Correccion de días en la gantt
2025-12-04 Final_pcb changes
2025-12-04 Borrado un archivo x
2025-12-08 added esp32 adc
2025-12-09 gui wifi
2025-12-09 push
2025-12-09 Sim actualizada
2025-12-10 Sim con divisor de voltaje
2025-12-10 Correcciones de ESR en sim sin divisor
2025-12-10 Multisim para el divisor de voltaje
2025-12-10 Agregao de amperimetros
2025-12-10 Agregado calculos de divisor de voltaje
2025-12-11 pcb bom
2025-12-13 Agrupando presentaciones
2025-12-13 attributes
2025-12-13 fix 2
2025-12-15 safety
2025-12-16 Valores obtenidos de practica
2025-12-16 simulaciones actualizadas
2025-12-16 temp changes
2025-12-18 Agregado de presentaciones
2025-12-18 new executable linux
2025-12-18 Final budget
2025-12-18 executable windows
2025-12-19 cambios de todo
2025-12-22 pcb fix
2026-01-06 erase material
